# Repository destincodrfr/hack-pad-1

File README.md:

# hack-pad-1
Hi this is my macropad 
please use responsibly

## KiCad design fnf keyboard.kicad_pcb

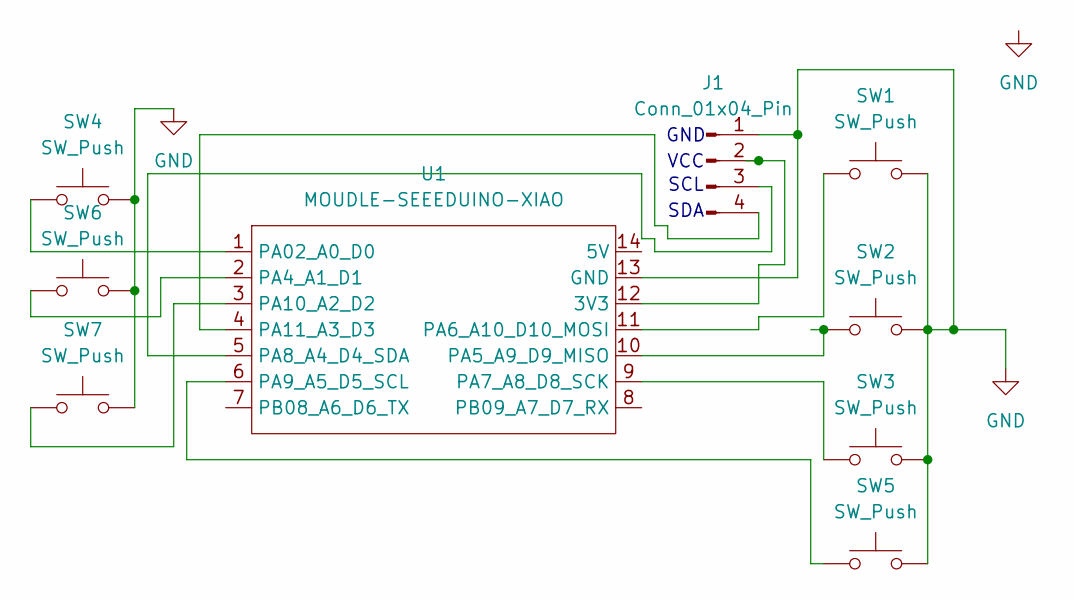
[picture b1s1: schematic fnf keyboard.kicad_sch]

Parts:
J1: Conn_01x04_Pin; PinHeader_1x04_P2.54mm_Vertical
SW1, SW2, SW3, SW4, SW5, SW6, SW7: SW_Push; SW_Cherry_MX_1.00u_PCB
U1: MOUDLE-SEEEDUINO-XIAO; XIAO-Generic-Hybrid-14P-2.54-21X17.8MM

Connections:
GND: J1.1, SW1.2, SW2.2, SW3.2, SW4.2, SW5.2, SW6.2, SW7.2, U1.13 (GND)
unnamed: J1.2, U1.12 (3V3)
unnamed: J1.3, U1.5 (PA8_A4_D4_SDA)
unnamed: J1.4, U1.4 (PA11_A3_D3)
unnamed: SW4.1, U1.1 (PA02_A0_D0)
unnamed: SW6.1, U1.2 (PA4_A1_D1)
unnamed: SW2.1, U1.10 (PA5_A9_D9_MISO)
unnamed: SW1.1, U1.11 (PA6_A10_D10_MOSI)
unnamed: SW3.1, U1.9 (PA7_A8_D8_SCK)
unnamed: SW5.1, U1.6 (PA9_A5_D5_SCL)
unnamed: SW7.1, U1.3 (PA10_A2_D2)

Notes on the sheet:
GND
SDA
VCC
SCL

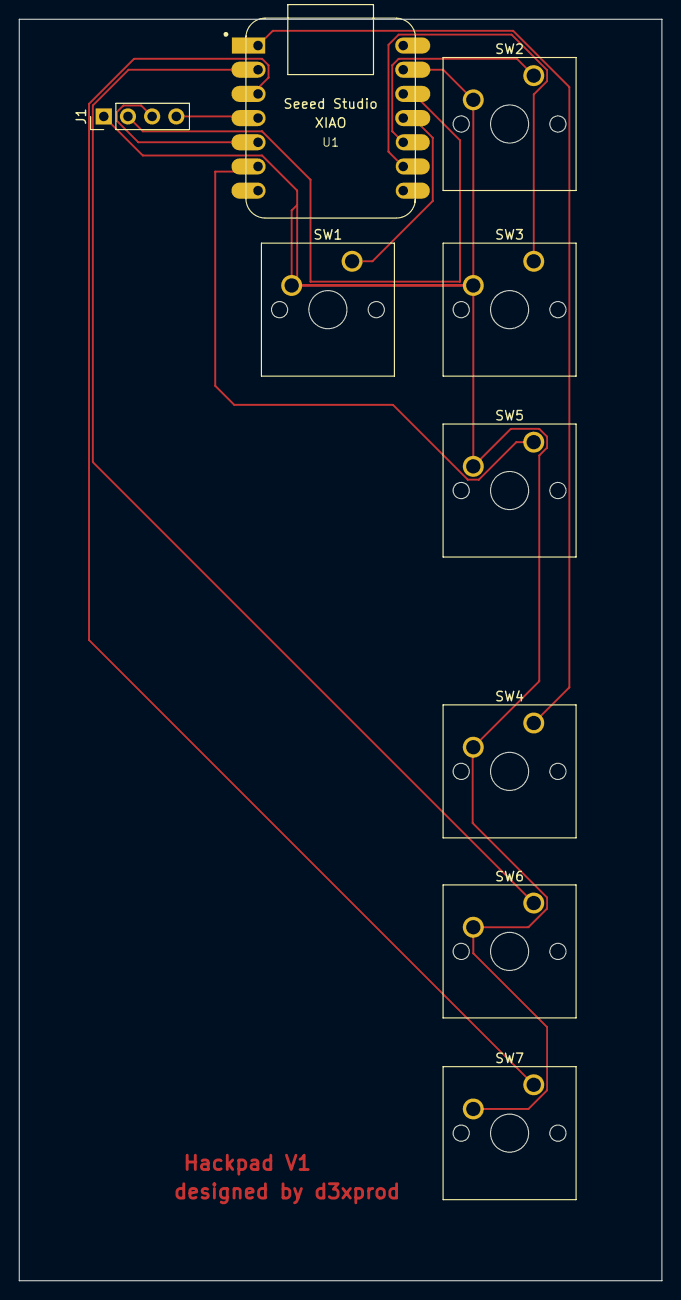
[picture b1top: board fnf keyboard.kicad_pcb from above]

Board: 2 copper layers, 67.5 x 132.5 mm, 9 parts (0 on the bottom side), 11 nets.
